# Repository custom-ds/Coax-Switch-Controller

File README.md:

# Coax Switch Controller

A WiFi-enabled coax antenna switch controller for amateur radio stations. It allows two radios to select one of six antennas each, with relay control driven by a custom PCB and an ESP32-based controller. The system supports both a front-panel interface and a built-in web UI / REST API.

## Overview

This project is designed to let a station operator:

- switch each radio between up to six antenna outputs
- optionally disconnect a radio from all antennas
- control the switch from the local front panel using a rotary knob and LCD
- control the switch from a browser or automation client over WiFi
- retain configuration and last-known antenna selections across reboots

The repository is divided into three main parts:

- [Firmware/](Firmware/) — ESP32 firmware for control logic, WiFi, API routes, and UI generation
- [Coax Switch Controller/](Coax%20Switch%20Controller/) — KiCad PCB design and fabrication outputs
- [3d Case/](3d%20Case/) — enclosure body, lid, and printable STL/BGCode exports

## Features

- Dual-radio antenna switching with six antenna positions per radio
- Shared collision protection so both radios cannot be assigned the same antenna simultaneously
- Persistent antenna state stored in ESP32 flash using Preferences
- Front-panel rotary knob and 16x2 LCD interface
- Built-in web interface served by the ESP32 itself
- REST-style API for external control and automation
- WiFi configuration with optional static IP support
- Custom relay-driver PCB design included in the repo

## Hardware

The firmware targets the SparkFun ESP32 Thing Plus C board. The controller also uses:

- SparkFun 16x2 SerLCD display
- SparkFun Qwiic Twist rotary knob
- custom relay driver PCB for switching the antenna control lines
- external 12V supply for the relay bank

The antenna switching model is based on two independent 3-bit select paths, one for each radio, with a shared latch/enable signal to prevent unstable switching during changes.

## Repository Layout

```text
.
├── Firmware/
│   ├── Firmware.ino
│   ├── config.h.template
│   ├── config.h
│   ├── README.md
│   └── LICENSE
├── Coax Switch Controller/
│   ├── Coax Switch Controller.kicad_pro
│   ├── Coax Switch Controller.kicad_sch
│   ├── Coax Switch Controller.kicad_pcb
│   ├── Bill of Materials.csv
│   └── Gerber/
├── 3d Case/
│   ├── Enclosure.FCStd
│   ├── Lid.FCStd
│   ├── .stl exports
│   └── related print files
├── README.md
├── test_config.html
├── test_interface.html
├── LICENSE
└── CLAUDE.md
```

## Firmware Build and Upload

The firmware is developed primarily in the Arduino IDE, although it can be edited in VS Code and uploaded from the Arduino IDE while both are pointed at the same .ino file.

### Required software

Install the following in the Arduino IDE:

1. ESP32 board package by Espressif Systems
2. Required libraries:
   - AsyncTCP
   - ESPAsyncTCP
   - ESPAsyncWebSrv
   - SparkFun Qwiic Twist Arduino Library
   - SparkFun SerLCD Arduino Library

### Important build flag for regex routes

The ESPAsyncWebSrv routes use regex matching for the API handlers. Without this flag, the web routes may silently fail to match.

For Arduino IDE, create or update the file:

- Windows: `%LOCALAPPDATA%\Arduino15\packages\espxxxx\hardware\espxxxx\{version}\platform.local.txt`
- Linux: `~/.arduino15/packages/espxxxx/hardware/espxxxx/{version}/platform.local.txt`

Add this line:

```text
compiler.cpp.extra_flags=-DASYNCWEBSERVER_REGEX=1
```

Then restart the Arduino IDE.

### Board selection and upload

1. Connect the ESP32 board over USB.
2. In Arduino IDE, choose the correct COM port.
3. Select the board: `SparkFun ESP32 Thing Plus C`.
4. Compile and upload the firmware.

> If the relay bank is already installed, the board may also require an external 12V input for the relay supply.

## Configuration

The firmware expects a local config file named `config.h` in [Firmware/](Firmware/). This file is intentionally gitignored and must be created from the template at [Firmware/config.h.template](Firmware/config.h.template).

The config file contains values for:

- WiFi SSID and password
- optional static IP configuration
- gateway, subnet, and DNS settings

Never commit the generated `config.h` file to version control.

## Web UI and API

The ESP32 serves a built-in web interface and REST-like endpoints for control and configuration. The firmware generates the HTML/CSS/JS dynamically rather than using a separate frontend project.

The repository also includes standalone browser preview files at the root:

- [test_interface.html](test_interface.html)
- [test_config.html](test_config.html)

These are useful for iterating on the interface layout without needing to flash the device each time.

## Front Panel Operation

The controller supports a front-panel workflow built around the rotary knob and LCD:

- normal mode allows selecting the active radio and changing the antenna
- the LCD shows current status and configuration information
- a long press enters configuration mode
- knob turns cycle through configuration screens
- a button click exits configuration mode and returns to the main operating view

## State Persistence

The controller stores persistent settings in the ESP32 `Preferences` namespace, including:

- last selected antenna per radio
- antenna names displayed in the UI
- LCD brightness and contrast settings
- knob RGB settings
- a long-lived API key

This ensures the device remembers its last configured state between power cycles.

## Project Notes

- There is no package manager or automated CI/test suite in this repo.
- Firmware development is hardware-focused and is flashed via the Arduino IDE.
- PCB and enclosure work is done in KiCad and FreeCAD, respectively.
- If the PCB or enclosure changes significantly, regenerate the output files manually so the exported fabrication artifacts remain consistent.

## More Information

For the most detailed firmware guidance, including required libraries, upload procedure, and environment setup, see [Firmware/README.md](Firmware/README.md).

For the PCB and enclosure sources, see:

- [Coax Switch Controller/](Coax%20Switch%20Controller/)
- [3d Case/](3d%20Case/)

## License

This project is distributed under the terms of the license included in [LICENSE](LICENSE).

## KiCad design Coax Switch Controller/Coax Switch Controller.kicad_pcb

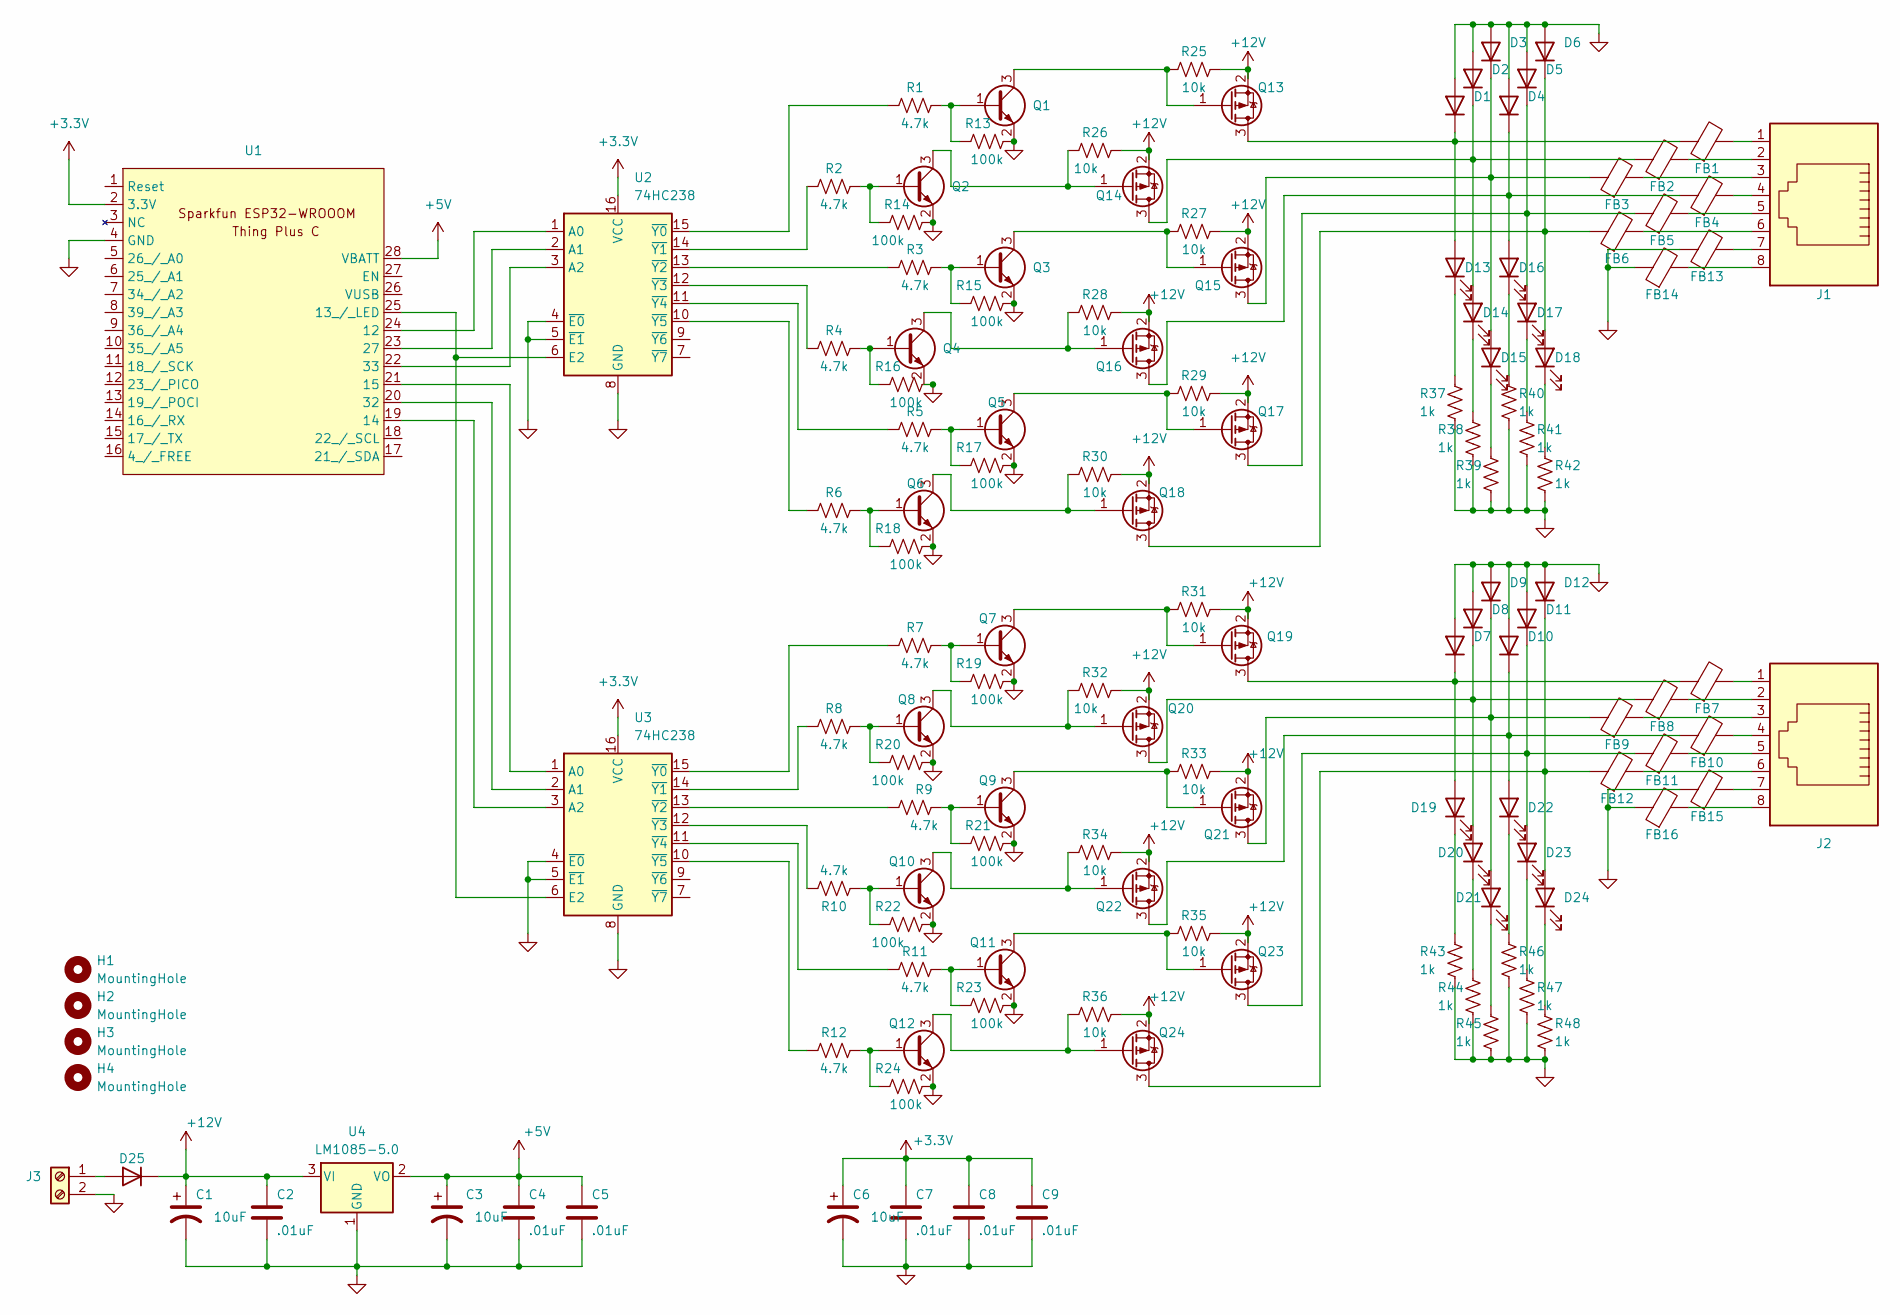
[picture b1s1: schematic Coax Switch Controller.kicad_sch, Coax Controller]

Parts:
C1, C3, C6: 10uF; CP_Elec_4x5.3
C2, C4, C5, C7, C8, C9: .01uF; C_0805_2012Metric_Pad1.18x1.45mm_HandSolder
D1, D2, D3, D4, D5, D6, D7, D8, D9, D10, D11, D12: MRA4007T3G; D_SOD-123F
D13, D14, D15, D16, D17, D18, D19, D20, D21, D22, D23, D24: LED; D_0805_2012Metric_Pad1.15x1.40mm_HandSolder
D25: 1N4007; D_SOD-123F
FB1, FB2, FB3, FB4, FB5, FB6, FB7, FB8, FB9, FB10, FB11, FB12, FB13, FB14, FB15, FB16: FerriteBead; L_0805_2012Metric_Pad1.05x1.20mm_HandSolder
H1, H2, H3, H4: MountingHole; MountingHole_3.2mm_M3
J1, J2: 8P8C; RJ45_Amphenol_54602-x08_Horizontal
J3: Screw_Terminal_01x02; TerminalBlock_RND_205-00001_1x02_P5.00mm_Horizontal
Q1, Q2, Q3, Q4, Q5, Q6, Q7, Q8, Q9, Q10, Q11, Q12: MMBT3904; SOT-23
Q13, Q14, Q15, Q16, Q17, Q18, Q19, Q20, Q21, Q22, Q23, Q24: DMP2004K-7; SOT-23
R1, R2, R3, R4, R5, R6, R7, R8, R9, R10, R11, R12: 4.7k; R_0805_2012Metric_Pad1.20x1.40mm_HandSolder
R13, R14, R15, R16, R17, R18, R19, R20, R21, R22, R23, R24: 100k; R_0805_2012Metric_Pad1.20x1.40mm_HandSolder
R25, R26, R27, R28, R29, R30, R31, R32, R33, R34, R35, R36: 10k; R_0805_2012Metric_Pad1.20x1.40mm_HandSolder
R37, R38, R39, R40, R41, R42, R43, R44, R45, R46, R47, R48: 1k; R_0805_2012Metric_Pad1.20x1.40mm_HandSolder
U1: ESP32-WROOM Thing Plus C
U2, U3: 74HC238; SOIC-16_3.9x9.9mm_P1.27mm
U4: LM1085-5.0; TO-263-3_TabPin2

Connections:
+3.3V: C6.1, C7.1, C8.1, C9.1, U1.2 (3.3V), U2.16 (VCC), U3.16 (VCC)
+5V: C3.1, C4.1, C5.1, U1.28 (VBATT), U4.2 (VO)
+12V: C1.1, C2.1, D25.1 (K), Q13.2 (S), Q14.2 (S), Q15.2 (S), Q16.2 (S), Q17.2 (S), Q18.2 (S), Q19.2 (S), Q20.2 (S), Q21.2 (S), Q22.2 (S), Q23.2 (S), Q24.2 (S), R25.2, R26.2, R27.2, R28.2, R29.2, R30.2, R31.2, R32.2, R33.2, R34.2, R35.2, R36.2, U4.3 (VI)
GND: C1.2, C2.2, C3.2, C4.2, C5.2, C6.2, C7.2, C8.2, C9.2, D1.2 (A), D2.2 (A), D3.2 (A), D4.2 (A), D5.2 (A), D6.2 (A), D7.2 (A), D8.2 (A), D9.2 (A), D10.2 (A), D11.2 (A), D12.2 (A), FB13.1, FB14.1, FB15.1, FB16.1, J3.2, Q1.2 (E), Q2.2 (E), Q3.2 (E), Q4.2 (E), Q5.2 (E), Q6.2 (E), Q7.2 (E), Q8.2 (E), Q9.2 (E), Q10.2 (E), Q11.2 (E), Q12.2 (E), R13.1, R14.1, R15.1, R16.1, R17.1, R18.1, R19.1, R20.1, R21.1, R22.1, R23.1, R24.1, R37.1, R38.1, R39.1, R40.1, R41.1, R42.1, R43.1, R44.1, R45.1, R46.1, R47.1, R48.1, U1.4 (GND), U2.4 (~E0), U2.5 (~E1), U2.8 (GND), U3.4 (~E0), U3.5 (~E1), U3.8 (GND), U4.1 (GND)
unnamed: D1.1 (K), D13.2 (A), FB1.1, Q13.3 (D)
unnamed: D10.1 (K), D22.2 (A), FB10.1, Q22.3 (D)
unnamed: D11.1 (K), D23.2 (A), FB11.1, Q23.3 (D)
unnamed: D12.1 (K), D24.2 (A), FB12.1, Q24.3 (D)
unnamed: D13.1 (K), R37.2
unnamed: D2.1 (K), D14.2 (A), FB2.1, Q14.3 (D)
unnamed: D14.1 (K), R38.2
unnamed: D3.1 (K), D15.2 (A), FB3.1, Q15.3 (D)
unnamed: D15.1 (K), R39.2
unnamed: D4.1 (K), D16.2 (A), FB4.1, Q16.3 (D)
unnamed: D16.1 (K), R40.2
unnamed: D5.1 (K), D17.2 (A), FB5.1, Q17.3 (D)
unnamed: D17.1 (K), R41.2
unnamed: D6.1 (K), D18.2 (A), FB6.1, Q18.3 (D)
unnamed: D18.1 (K), R42.2
unnamed: D7.1 (K), D19.2 (A), FB7.1, Q19.3 (D)
unnamed: D19.1 (K), R43.2
unnamed: D8.1 (K), D20.2 (A), FB8.1, Q20.3 (D)
unnamed: D20.1 (K), R44.2
unnamed: D9.1 (K), D21.2 (A), FB9.1, Q21.3 (D)
unnamed: D21.1 (K), R45.2
unnamed: D22.1 (K), R46.2
unnamed: D23.1 (K), R47.2
unnamed: D24.1 (K), R48.2
unnamed: D25.2 (A), J3.1
unnamed: FB1.2, J1.1
unnamed: FB2.2, J1.2
unnamed: FB3.2, J1.3
unnamed: FB4.2, J1.4
unnamed: FB5.2, J1.5
unnamed: FB6.2, J1.6
unnamed: FB7.2, J2.1
unnamed: FB8.2, J2.2
unnamed: FB9.2, J2.3
unnamed: FB10.2, J2.4
unnamed: FB11.2, J2.5
unnamed: FB12.2, J2.6
unnamed: FB13.2, J1.7
unnamed: FB14.2, J1.8
unnamed: FB15.2, J2.7
unnamed: FB16.2, J2.8
unnamed: Q1.1 (B), R1.2, R13.2
unnamed: Q1.3 (C), Q13.1 (G), R25.1
unnamed: Q2.1 (B), R2.2, R14.2
unnamed: Q3.1 (B), R3.2, R15.2
unnamed: Q4.1 (B), R4.2, R16.2
unnamed: Q5.1 (B), R5.2, R17.2
unnamed: Q6.1 (B), R6.2, R18.2
unnamed: Q7.1 (B), R7.2, R19.2
unnamed: Q8.1 (B), R8.2, R20.2
unnamed: Q9.1 (B), R9.2, R21.2
unnamed: Q10.1 (B), R10.2, R22.2
unnamed: Q10.3 (C), Q22.1 (G), R34.1
unnamed: Q11.1 (B), R11.2, R23.2
unnamed: Q11.3 (C), Q23.1 (G), R35.1
unnamed: Q12.1 (B), R12.2, R24.2
unnamed: Q12.3 (C), Q24.1 (G), R36.1
unnamed: Q2.3 (C), Q14.1 (G), R26.1
unnamed: Q3.3 (C), Q15.1 (G), R27.1
unnamed: Q4.3 (C), Q16.1 (G), R28.1
unnamed: Q5.3 (C), Q17.1 (G), R29.1
unnamed: Q6.3 (C), Q18.1 (G), R30.1
unnamed: Q7.3 (C), Q19.1 (G), R31.1
unnamed: Q8.3 (C), Q20.1 (G), R32.1
unnamed: Q9.3 (C), Q21.1 (G), R33.1
unnamed: U1.24 (12), U2.1 (A0)
unnamed: U1.25 (13_/_LED), U2.6 (E2), U3.6 (E2)
unnamed: U1.19 (14), U3.3 (A2)
unnamed: U1.21 (15), U3.1 (A0)
unnamed: U1.23 (27), U2.2 (A1)
unnamed: U1.20 (32), U3.2 (A1)
unnamed: U1.22 (33), U2.3 (A2)
unnamed: R1.1, U2.15 (~Y0)
unnamed: R2.1, U2.14 (~Y1)
unnamed: R3.1, U2.13 (~Y2)
unnamed: R4.1, U2.12 (~Y3)
unnamed: R5.1, U2.11 (~Y4)
unnamed: R6.1, U2.10 (~Y5)
unnamed: R7.1, U3.15 (~Y0)
unnamed: R8.1, U3.14 (~Y1)
unnamed: R9.1, U3.13 (~Y2)
unnamed: R10.1, U3.12 (~Y3)
unnamed: R11.1, U3.11 (~Y4)
unnamed: R12.1, U3.10 (~Y5)

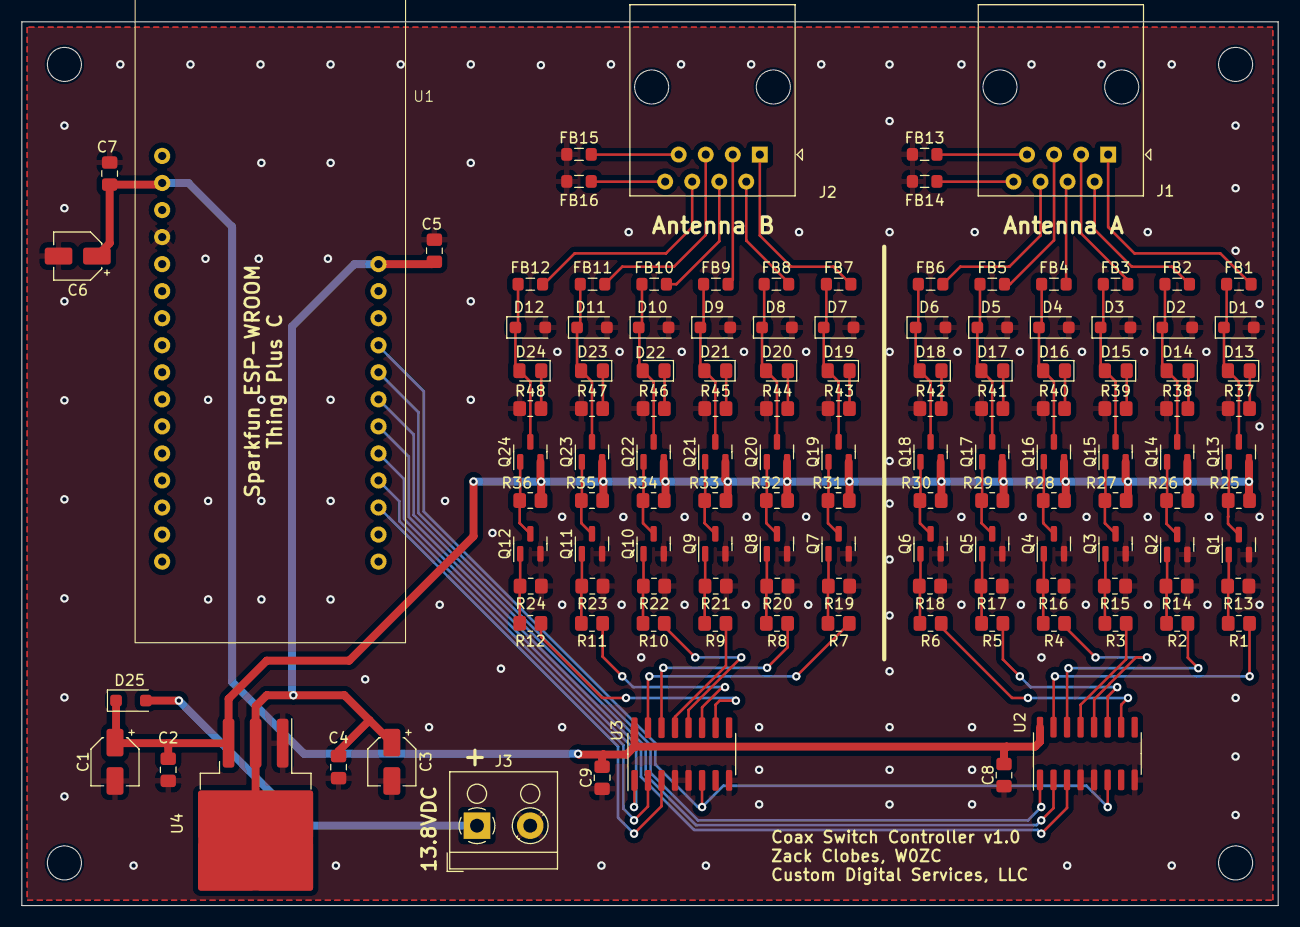
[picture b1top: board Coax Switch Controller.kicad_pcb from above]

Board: 2 copper layers, 118.0 x 83.0 mm, 133 parts (0 on the bottom side), 88 nets.

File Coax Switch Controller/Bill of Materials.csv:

"Reference","Value","Datasheet","Footprint","Qty","DNP","DigiKey-PN","SparkFun-PN"
"C1,C3,C6","10uF","~","Capacitor_SMD:CP_Elec_4x5.3","3","","PCE3795CT-ND",""
"C2,C4,C5,C7,C8,C9",".01uF","~","Capacitor_SMD:C_0805_2012Metric_Pad1.18x1.45mm_HandSolder","6","","C0603C103J5REC7411",""
"D1,D2,D3,D4,D5,D6,D7,D8,D9,D10,D11,D12,D25","1N4007","-- mixed values --","Diode_SMD:D_SOD-123F","13","","1655-1N4007FLCT-ND",""
"D13,D14,D15,D16,D17,D18,D19,D20,D21,D22,D23,D24","LED","~","Diode_SMD:D_0805_2012Metric_Pad1.15x1.40mm_HandSolder","12","","732-4985-1-ND",""
"FB1,FB2,FB3,FB4,FB5,FB6,FB7,FB8,FB9,FB10,FB11,FB12,FB13,FB14,FB15,FB16","FerriteBead","~","Inductor_SMD:L_0805_2012Metric_Pad1.05x1.20mm_HandSolder","16","","240-2411-1-ND",""
"H1,H2,H3,H4","MountingHole","~","MountingHole:MountingHole_3.2mm_M3","4","","",""
"J1,J2","8P8C","~","Connector_RJ:RJ45_Amphenol_54602-x08_Horizontal","2","","609-1046-ND",""
"J3","Screw_Terminal_01x02","~","TerminalBlock_RND:TerminalBlock_RND_205-00001_1x02_P5.00mm_Horizontal","1","","732-10955-ND",""
"Q1,Q2,Q3,Q4,Q5,Q6,Q7,Q8,Q9,Q10,Q11,Q12","MMBT3904","https://www.onsemi.com/pdf/datasheet/pzt3904-d.pdf","Package_TO_SOT_SMD:SOT-23","12","","MMBT3904TPMSCT-ND",""
"Q13,Q14,Q15,Q16,Q17,Q18,Q19,Q20,Q21,Q22,Q23,Q24","DMP2004K-7","","Package_TO_SOT_SMD:SOT-23","12","","DMP2004KDICT-ND",""
"R1,R2,R3,R4,R5,R6,R7,R8,R9,R10,R11,R12","4.7k","~","Resistor_SMD:R_0805_2012Metric_Pad1.20x1.40mm_HandSolder","12","","311-4.70KCRCT-ND",""
"R13,R14,R15,R16,R17,R18,R19,R20,R21,R22,R23,R24","100k","~","Resistor_SMD:R_0805_2012Metric_Pad1.20x1.40mm_HandSolder","12","","311-100KARCT-ND",""
"R25,R26,R27,R28,R29,R30,R31,R32,R33,R34,R35,R36","10k","~","Resistor_SMD:R_0805_2012Metric_Pad1.20x1.40mm_HandSolder","12","","311-10.0KCRCT-ND",""
"R37,R38,R39,R40,R41,R42,R43,R44,R45,R46,R47,R48","1k","~","Resistor_SMD:R_0805_2012Metric_Pad1.20x1.40mm_HandSolder","12","","311-1.00KCRCT-ND",""
"U1","~","","Custom DS:ESP32-WROOM Thing Plus C","1","","","SPX-18018"
"U2,U3","74HC238","http://www.ti.com/lit/ds/symlink/cd74hc238.pdf","Package_SO:SOIC-16_3.9x9.9mm_P1.27mm","2","","296-9188-5-ND",""
"U4","LM1085-5.0","http://www.ti.com/lit/ds/symlink/lm1085.pdf","Package_TO_SOT_SMD:TO-263-3_TabPin2","1","","LM1086ISX-5.0/NOPBCT-ND",""

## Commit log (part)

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2024-04-08 Initial Project upload
2024-04-18 Implemented basic API functionality. Cleaned code
2024-04-20 Updated to SerLCD library. Implemented customizable antenna port names.
2024-04-20 Basic web page functionlity running
2024-04-21 Added interface screen.
2024-04-21 Added configuration screens to monitor settings.
2024-04-27 Finalized version 1.0.1 of firmware. Updated the lid STL.
    Lid now has a better fit and avoids the LCD circuit board inside the front panel.
2024-05-06 Firmware release 1.0.1. Standardizing interfaces.
2024-08-29 Minor updates to PCB
2024-09-09 Updated to Kicad 8. Added bill of materials, and PCB's of the output.
